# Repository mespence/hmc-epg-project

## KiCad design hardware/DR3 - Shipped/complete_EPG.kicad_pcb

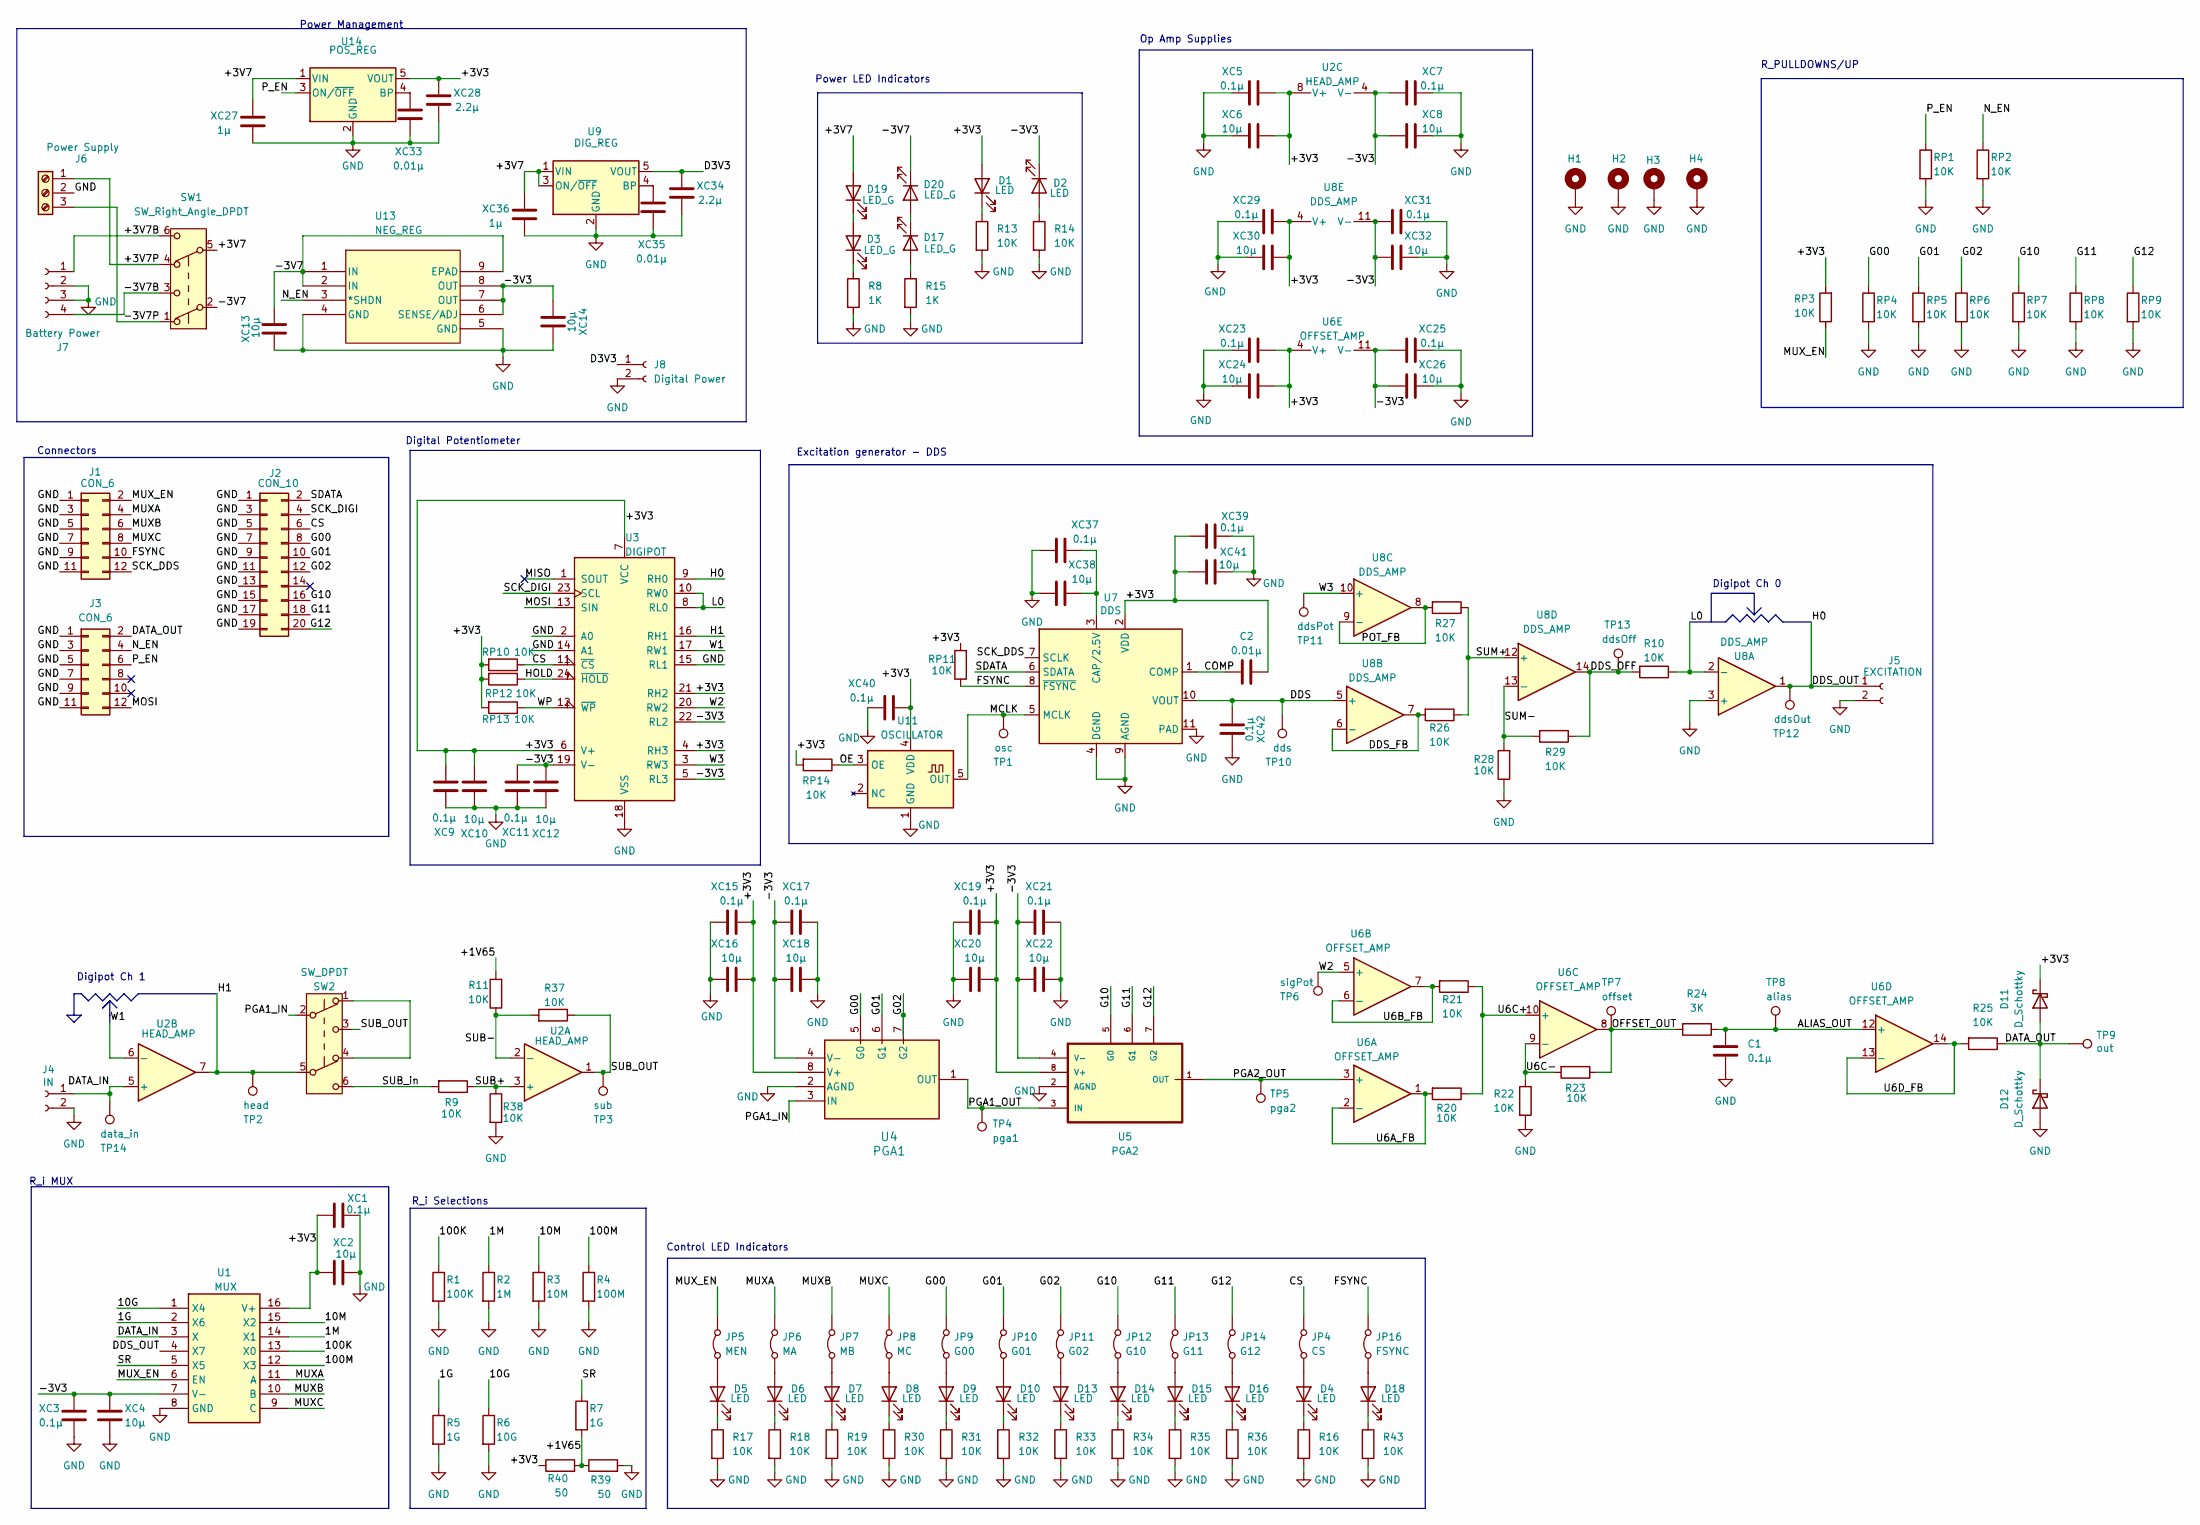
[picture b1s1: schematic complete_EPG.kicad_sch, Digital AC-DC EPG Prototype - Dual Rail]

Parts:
C1: 0.1μ; C_0805_2012Metric_Pad1.18x1.45mm_HandSolder
C2: 0.01μ; C_0805_2012Metric_Pad1.18x1.45mm_HandSolder
D1, D2, D4, D5, D6, D7, D8, D9, D10, D13, D14, D15, D16, D18: LED; LED_0805_2012Metric_Pad1.15x1.40mm_HandSolder; Mfg Part # LTST-C171KRKT
D3, D17, D19, D20: LED_G; LED_0805_2012Metric_Pad1.15x1.40mm_HandSolder; Mfg Part # LTST-C170KGKT
D11, D12: D_Schottky; D_0805_2012Metric_Pad1.15x1.40mm_HandSolder; Mfg Part # SD0805S040S0R1
H1, H2, H3, H4: MountingHole_Pad; MountingHole_3.2mm_M3_DIN965_Pad
J1, J3: CON_6; PinHeader_2x06_P2.54mm_Vertical; Mfg Part # IDSD-06-D-02.00-G
J2: CON_10; PinHeader_2x10_P2.54mm_Vertical; Mfg Part # IDSD-10-D-02.00-T-G
J4: IN; Right angle BNC 0731010120; Mfg Part # 0731010120
J5: EXCITATION; Right angle BNC 0731010120; Mfg Part # 0731010120
J6: Power Supply; Screw_Terminal_Power_Supply; Mfg Part # 1729131
J7: Battery Power; Screw_Terminal_Battery; Mfg Part # OSTVN04A150
J8: Digital Power; Screw_Terminal_Digital_Board; Mfg Part # OSTVN02A150
JP4: CS; SolderJumper-2_P1.3mm_Bridged_RoundedPad1.0x1.5mm
JP5: MEN; SolderJumper-2_P1.3mm_Bridged_RoundedPad1.0x1.5mm
JP6: MA; SolderJumper-2_P1.3mm_Bridged_RoundedPad1.0x1.5mm
JP7: MB; SolderJumper-2_P1.3mm_Bridged_RoundedPad1.0x1.5mm
JP8: MC; SolderJumper-2_P1.3mm_Bridged_RoundedPad1.0x1.5mm
JP9: G00; SolderJumper-2_P1.3mm_Bridged_RoundedPad1.0x1.5mm
JP10: G01; SolderJumper-2_P1.3mm_Bridged_RoundedPad1.0x1.5mm
JP11: G02; SolderJumper-2_P1.3mm_Bridged_RoundedPad1.0x1.5mm
JP12: G10; SolderJumper-2_P1.3mm_Bridged_RoundedPad1.0x1.5mm
JP13: G11; SolderJumper-2_P1.3mm_Bridged_RoundedPad1.0x1.5mm
JP14: G12; SolderJumper-2_P1.3mm_Bridged_RoundedPad1.0x1.5mm
JP16: FSYNC; SolderJumper-2_P1.3mm_Bridged_RoundedPad1.0x1.5mm
R1: 100K; R_0805_2012Metric_Pad1.20x1.40mm_HandSolder
R2: 1M; R_0805_2012Metric_Pad1.20x1.40mm_HandSolder
R3: 10M; R_0805_2012Metric_Pad1.20x1.40mm_HandSolder
R4: 100M; R_0805_2012Metric_Pad1.20x1.40mm_HandSolder
R5, R7: 1G; R_0805_2012Metric_Pad1.20x1.40mm_HandSolder
R6: 10G; R_0805_2012Metric_Pad1.20x1.40mm_HandSolder
R8, R15: 1K; R_0805_2012Metric_Pad1.20x1.40mm_HandSolder
R9, R10, R11, R13, R14, R16, R17, R18, R19, R20, R21, R22, R23, R25, R26, R27, R28, R29, R30, R31, R32, R33, R34, R35, R36, R37, R38, R43: 10K; R_0805_2012Metric_Pad1.20x1.40mm_HandSolder
R24: 3K; R_0805_2012Metric_Pad1.20x1.40mm_HandSolder
R39, R40: 50; R_0805_2012Metric_Pad1.20x1.40mm_HandSolder
RP1, RP2, RP3, RP4, RP5, RP6, RP7, RP8, RP9, RP10, RP11, RP12, RP13, RP14: 10K; R_0805_2012Metric_Pad1.20x1.40mm_HandSolder
SW1: SW_Right_Angle_DPDT; SW_E-Switch_EG2219_DPDT_Angled; Mfg Part # EG2219
SW2: SW_DPDT; SW_CK_JS202011CQN_DPDT_Straight; Mfg Part # JS202011CQN
TP1: osc; TestPoint_Pad_2.0x2.0mm
TP2: head; TestPoint_Pad_2.0x2.0mm
TP3: sub; TestPoint_Pad_2.0x2.0mm
TP4: pga1; TestPoint_Pad_2.0x2.0mm
TP5: pga2; TestPoint_Pad_2.0x2.0mm
TP6: sigPot; TestPoint_Pad_2.0x2.0mm
TP7: offset; TestPoint_Pad_2.0x2.0mm
TP8: alias; TestPoint_Pad_2.0x2.0mm
TP9: out; TestPoint_Pad_2.0x2.0mm
TP10: dds; TestPoint_Pad_2.0x2.0mm
TP11: ddsPot; TestPoint_Pad_2.0x2.0mm
TP12: ddsOut; TestPoint_Pad_2.0x2.0mm
TP13: ddsOff; TestPoint_Pad_2.0x2.0mm
TP14: data_in; TestPoint_Pad_2.0x2.0mm
U1: MUX; LIB_DG4051EEY-T1-GE3; Mfg Part # DG4051EEY-T1-GE3
U2: HEAD_AMP; SOIC-8_3.9x4.9mm_P1.27mm; Mfg Part # LMC662CMX/NOPB
U3: DIGIPOT; SOIC-24W_7.5x15.4mm_P1.27mm; Mfg Part # X9250US24Z-2.7T1
U4: PGA1; TSOT-23-8; Mfg Part # LTC6910-3CTS8-TRMPBF
U5: PGA2; TSOT-23-8; Mfg Part # LTC6910-1CTS8#PBF
U6: OFFSET_AMP; SOIC-14_3.9x8.7mm_P1.27mm; Mfg Part # TLV9104IDR
U7: DDS; LFCSP-WD-10-1EP_3x3mm_P0.5mm_EP1.64x2.38mm; Mfg Part # AD9837BCPZ-RL7
U8: DDS_AMP; SOIC-14_3.9x8.7mm_P1.27mm; Mfg Part # TLV9104IDR
U9: DIG_REG; SOT-23-5; Mfg Part # LP2985-33DBVRM3
U11: OSCILLATOR; TSOT-23-5; Mfg Part # SIT2024BIAS1-33E-16.000000
U13: NEG_REG; DFN-8_DD_LIT; Mfg Part # LT3015EDD-3.3#PBF
U14: POS_REG; SOT-23-5; Mfg Part # LP2985A-33DBVRM3
XC1, XC3, XC5, XC7, XC9, XC11, XC15, XC17, XC19, XC21, XC23, XC25, XC29, XC31, XC37, XC39, XC40, XC42: 0.1μ; C_0805_2012Metric_Pad1.18x1.45mm_HandSolder
XC2, XC4, XC6, XC8, XC10, XC12, XC13, XC14, XC16, XC18, XC20, XC22, XC24, XC26, XC30, XC32, XC38, XC41: 10μ; C_0805_2012Metric_Pad1.18x1.45mm_HandSolder
XC27, XC36: 1μ; C_0805_2012Metric_Pad1.18x1.45mm_HandSolder
XC28, XC34: 2.2μ; C_0805_2012Metric_Pad1.18x1.45mm_HandSolder
XC33, XC35: 0.01μ; C_0805_2012Metric_Pad1.18x1.45mm_HandSolder

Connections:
/1G: R5.1, U1.2 (X6)
/1M: R2.1, U1.14 (X1)
/10G: R6.1, U1.1 (X4)
/10M: R3.1, U1.15 (X2)
/100K: R1.1, U1.13 (X0)
/100M: R4.1, U1.12 (X3)
/+1V65: R7.2, R11.2, R39.1, R40.2
/+3V3: C2.2, D1.2 (A), D11.1 (K), R40.1, RP3.2, RP10.2, RP11.2, RP12.2, RP13.2, RP14.2, U1.16 (V+), U2.8 (V+), U3.4 (RH3), U3.6 (V+), U3.7 (VCC), U3.21 (RH2), U4.8 (V+), U5.8 (V+), U6.4 (V+), U7.2 (VDD), U8.4 (V+), U11.4 (VDD), U14.5 (VOUT), XC1.1, XC2.1, XC5.2, XC6.2, XC9.1, XC10.1, XC15.2, XC16.2, XC19.2, XC20.2, XC23.2, XC24.2, XC28.2, XC29.2, XC30.2, XC39.1, XC40.1, XC41.1
/+3V7: D19.2 (A), SW1.5 (B), U9.1 (VIN), U9.3 (ON/~OFF), U14.1 (VIN), XC27.2, XC36.2
/+3V7B: J7.1, SW1.6 (C)
/+3V7P: J6.1, SW1.4 (A)
/-3V3: D2.1 (K), U1.7 (V-), U2.4 (V-), U3.5 (RL3), U3.19 (V-), U3.22 (RL2), U4.4 (V-), U5.4 (V-), U6.11 (V-), U8.11 (V-), U13.6 (SENSE/ADJ), U13.7 (OUT), U13.8 (OUT), XC3.1, XC4.1, XC7.1, XC8.1, XC11.1, XC12.1, XC14.2, XC17.1, XC18.1, XC21.1, XC22.1, XC25.1, XC26.1, XC31.1, XC32.1
/-3V7: D20.1 (K), SW1.2 (B), U13.1 (IN), U13.2 (IN), U13.9 (EPAD), XC13.2
/-3V7B: J7.4, SW1.3 (C)
/-3V7P: J6.3, SW1.1 (A)
/ALIAS_OUT: C1.2, R24.1, TP8.1, U6.12 (+)
/COMP: C2.1, U7.1 (COMP)
/CS: J2.6, JP4.2 (B), RP10.1, U3.11 (~CS)
/D3V3: J8.1, U9.5 (VOUT), XC34.2
/DATA_IN: J4.1, TP14.1, U1.3 (X), U2.5 (+)
/DATA_OUT: D11.2 (A), D12.1 (K), J3.2, R25.1, TP9.1
/DDS: TP10.1, U7.10 (VOUT), U8.5 (+), XC42.1
/DDS_FB: R26.2, U8.6 (-), U8.7
/DDS_OFF: R10.2, R29.1, TP13.1, U8.14
/DDS_OUT: J5.1, TP12.1, U1.4 (X7), U3.9 (RH0), U8.1
/FSYNC: J1.10, JP16.2 (B), RP11.1, U7.8 (~FSYNC)
/G00: J2.8, JP9.2 (B), RP4.1, U4.5 (G0)
/G01: J2.10, JP10.2 (B), RP5.1, U4.6 (G1)
/G02: J2.12, JP11.2 (B), RP6.1, U4.7 (G2)
/G10: J2.16, JP12.2 (B), RP7.1, U5.5 (G0)
/G11: J2.18, JP13.2 (B), RP8.1, U5.6 (G1)
/G12: J2.20, JP14.2 (B), RP9.1, U5.7 (G2)
/H1: SW2.5 (B), TP2.1, U2.7, U3.16 (RH1)
/HOLD: RP12.1, U3.24 (~HOLD)
/L0: R10.1, U3.8 (RL0), U3.10 (RW0), U8.2 (-)
/MCLK: TP1.1, U7.5 (MCLK), U11.5 (OUT)
/MISO: U3.1 (SOUT)
/MOSI: J3.12, U3.13 (SIN)
/MUXA: J1.4, JP6.2 (B), U1.11 (A)
/MUXB: J1.6, JP7.2 (B), U1.10 (B)
/MUXC: J1.8, JP8.2 (B), U1.9 (C)
/MUX_EN: J1.2, JP5.2 (B), RP3.1, U1.6 (EN)
/N_EN: J3.4, RP2.1, U13.3 (*SHDN)
/OE: RP14.1, U11.3 (OE)
/OFFSET_OUT: R23.1, R24.2, TP7.1, U6.8
/PGA1_IN: SW2.2 (B), U4.3 (IN)
/PGA1_OUT: TP4.1, U4.1 (OUT), U5.3 (IN)
/PGA2_OUT: TP5.1, U5.1 (OUT), U6.3 (+)
/POT_FB: R27.2, U8.8, U8.9 (-)
/P_EN: J3.6, RP1.1, U14.3 (ON/~OFF)
/SCK_DDS: J1.12, U7.7 (SCLK)
/SCK_DIGI: J2.4, U3.23 (SCL)
/SDATA: J2.2, U7.6 (SDATA)
/SR: R7.1, U1.5 (X5)
/SUB+: R9.1, R38.1, U2.3 (+)
/SUB-: R11.1, R37.2, U2.2 (-)
/SUB_OUT: R37.1, SW2.3 (C), TP3.1, U2.1
/SUB_in: R9.2, SW2.6 (C)
/SUM+: R26.1, R27.1, U8.12 (+)
/SUM-: R28.2, R29.2, U8.13 (-)
/U6A_FB: R20.2, U6.1, U6.2 (-)
/U6B_FB: R21.2, U6.6 (-), U6.7
/U6C+: R20.1, R21.1, U6.10 (+)
/U6C-: R22.1, R23.2, U6.9 (-)
/U6D_FB: R25.2, U6.13 (-), U6.14
/W1: U2.6 (-), U3.17 (RW1)
/W2: TP6.1, U3.20 (RW2), U6.5 (+)
/W3: TP11.1, U3.3 (RW3), U8.10 (+)
/WP: RP13.1, U3.12 (~WP)
GND: C1.1, D12.2 (A), H1.1, H2.1, H3.1, H4.1, J1.1, J1.3, J1.5, J1.7, J1.9, J1.11, J2.1, J2.3, J2.5, J2.7, J2.9, J2.11, J2.13, J2.15, J2.17, J2.19, J3.1, J3.3, J3.5, J3.7, J3.9, J3.11, J4.2, J5.2, J6.2, J7.2, J7.3, J8.2, R1.2, R2.2, R3.2, R4.2, R5.2, R6.2, R8.2, R13.2, R14.2, R15.2, R16.2, R17.2, R18.2, R19.2, R22.2, R28.1, R30.2, R31.2, R32.2, R33.2, R34.2, R35.2, R36.2, R38.2, R39.2, R43.2, RP1.2, RP2.2, RP4.2, RP5.2, RP6.2, RP7.2, RP8.2, RP9.2, U1.8 (GND), U3.2 (A0), U3.14 (A1), U3.15 (RL1), U3.18 (VSS), U4.2 (AGND), U5.2 (AGND), U7.4 (DGND), U7.9 (AGND), U7.11 (PAD), U8.3 (+), U9.2 (GND), U11.1 (GND), U13.4 (GND), U13.5 (GND), U14.2 (GND), XC1.2, XC2.2, XC3.2, XC4.2, XC5.1, XC6.1, XC7.2, XC8.2, XC9.2, XC10.2, XC11.2, XC12.2, XC13.1, XC14.1, XC15.1, XC16.1, XC17.2, XC18.2, XC19.1, XC20.1, XC21.2, XC22.2, XC23.1, XC24.1, XC25.2, XC26.2, XC27.1, XC28.1, XC29.1, XC30.1, XC31.2, XC32.2, XC33.1, XC34.1, XC35.1, XC36.1, XC37.2, XC38.2, XC39.2, XC40.2, XC41.2, XC42.2
unnamed: D1.1 (K), R13.1
unnamed: D2.2 (A), R14.1
unnamed: D3.1 (K), R8.1
unnamed: D4.2 (A), JP4.1 (A)
unnamed: D4.1 (K), R16.1
unnamed: D5.2 (A), JP5.1 (A)
unnamed: D5.1 (K), R17.1
unnamed: D6.2 (A), JP6.1 (A)
unnamed: D6.1 (K), R18.1
unnamed: D7.2 (A), JP7.1 (A)
unnamed: D7.1 (K), R19.1
unnamed: D8.2 (A), JP8.1 (A)
unnamed: D8.1 (K), R30.1
unnamed: D9.2 (A), JP9.1 (A)
unnamed: D9.1 (K), R31.1
unnamed: D10.2 (A), JP10.1 (A)
unnamed: D10.1 (K), R32.1
unnamed: D13.2 (A), JP11.1 (A)
unnamed: D13.1 (K), R33.1
unnamed: D14.2 (A), JP12.1 (A)
unnamed: D14.1 (K), R34.1
unnamed: D15.2 (A), JP13.1 (A)
unnamed: D15.1 (K), R35.1
unnamed: D16.2 (A), JP14.1 (A)
unnamed: D16.1 (K), R36.1
unnamed: D17.2 (A), R15.1
unnamed: D17.1 (K), D20.2 (A)
unnamed: D18.2 (A), JP16.1 (A)
unnamed: D18.1 (K), R43.1
unnamed: D3.2 (A), D19.1 (K)
unnamed: SW2.1 (A), SW2.4 (A)
unnamed: U7.3 (CAP/2.5V), XC37.1, XC38.1
unnamed: U9.4 (BP), XC35.2
unnamed: U14.4 (BP), XC33.2

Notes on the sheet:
Digital Potentiometer
Digipot Ch 1
R_PULLDOWNS/UP
Op Amp Supplies
Connectors
Power LED Indicators
R_i Selections
Power Management
Digipot Ch 0
Control LED Indicators
R_i MUX
Excitation generator - DDS

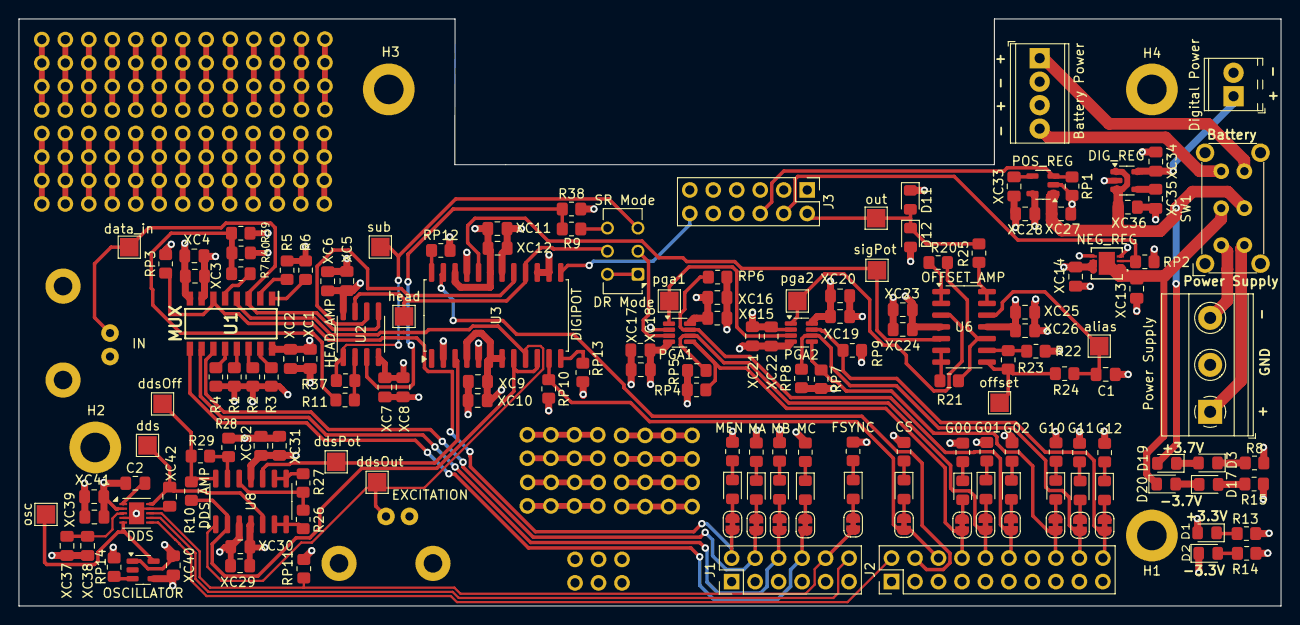
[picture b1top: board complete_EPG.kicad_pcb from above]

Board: 4 copper layers, 136.5 x 63.5 mm, 170 parts (0 on the bottom side), 103 nets.

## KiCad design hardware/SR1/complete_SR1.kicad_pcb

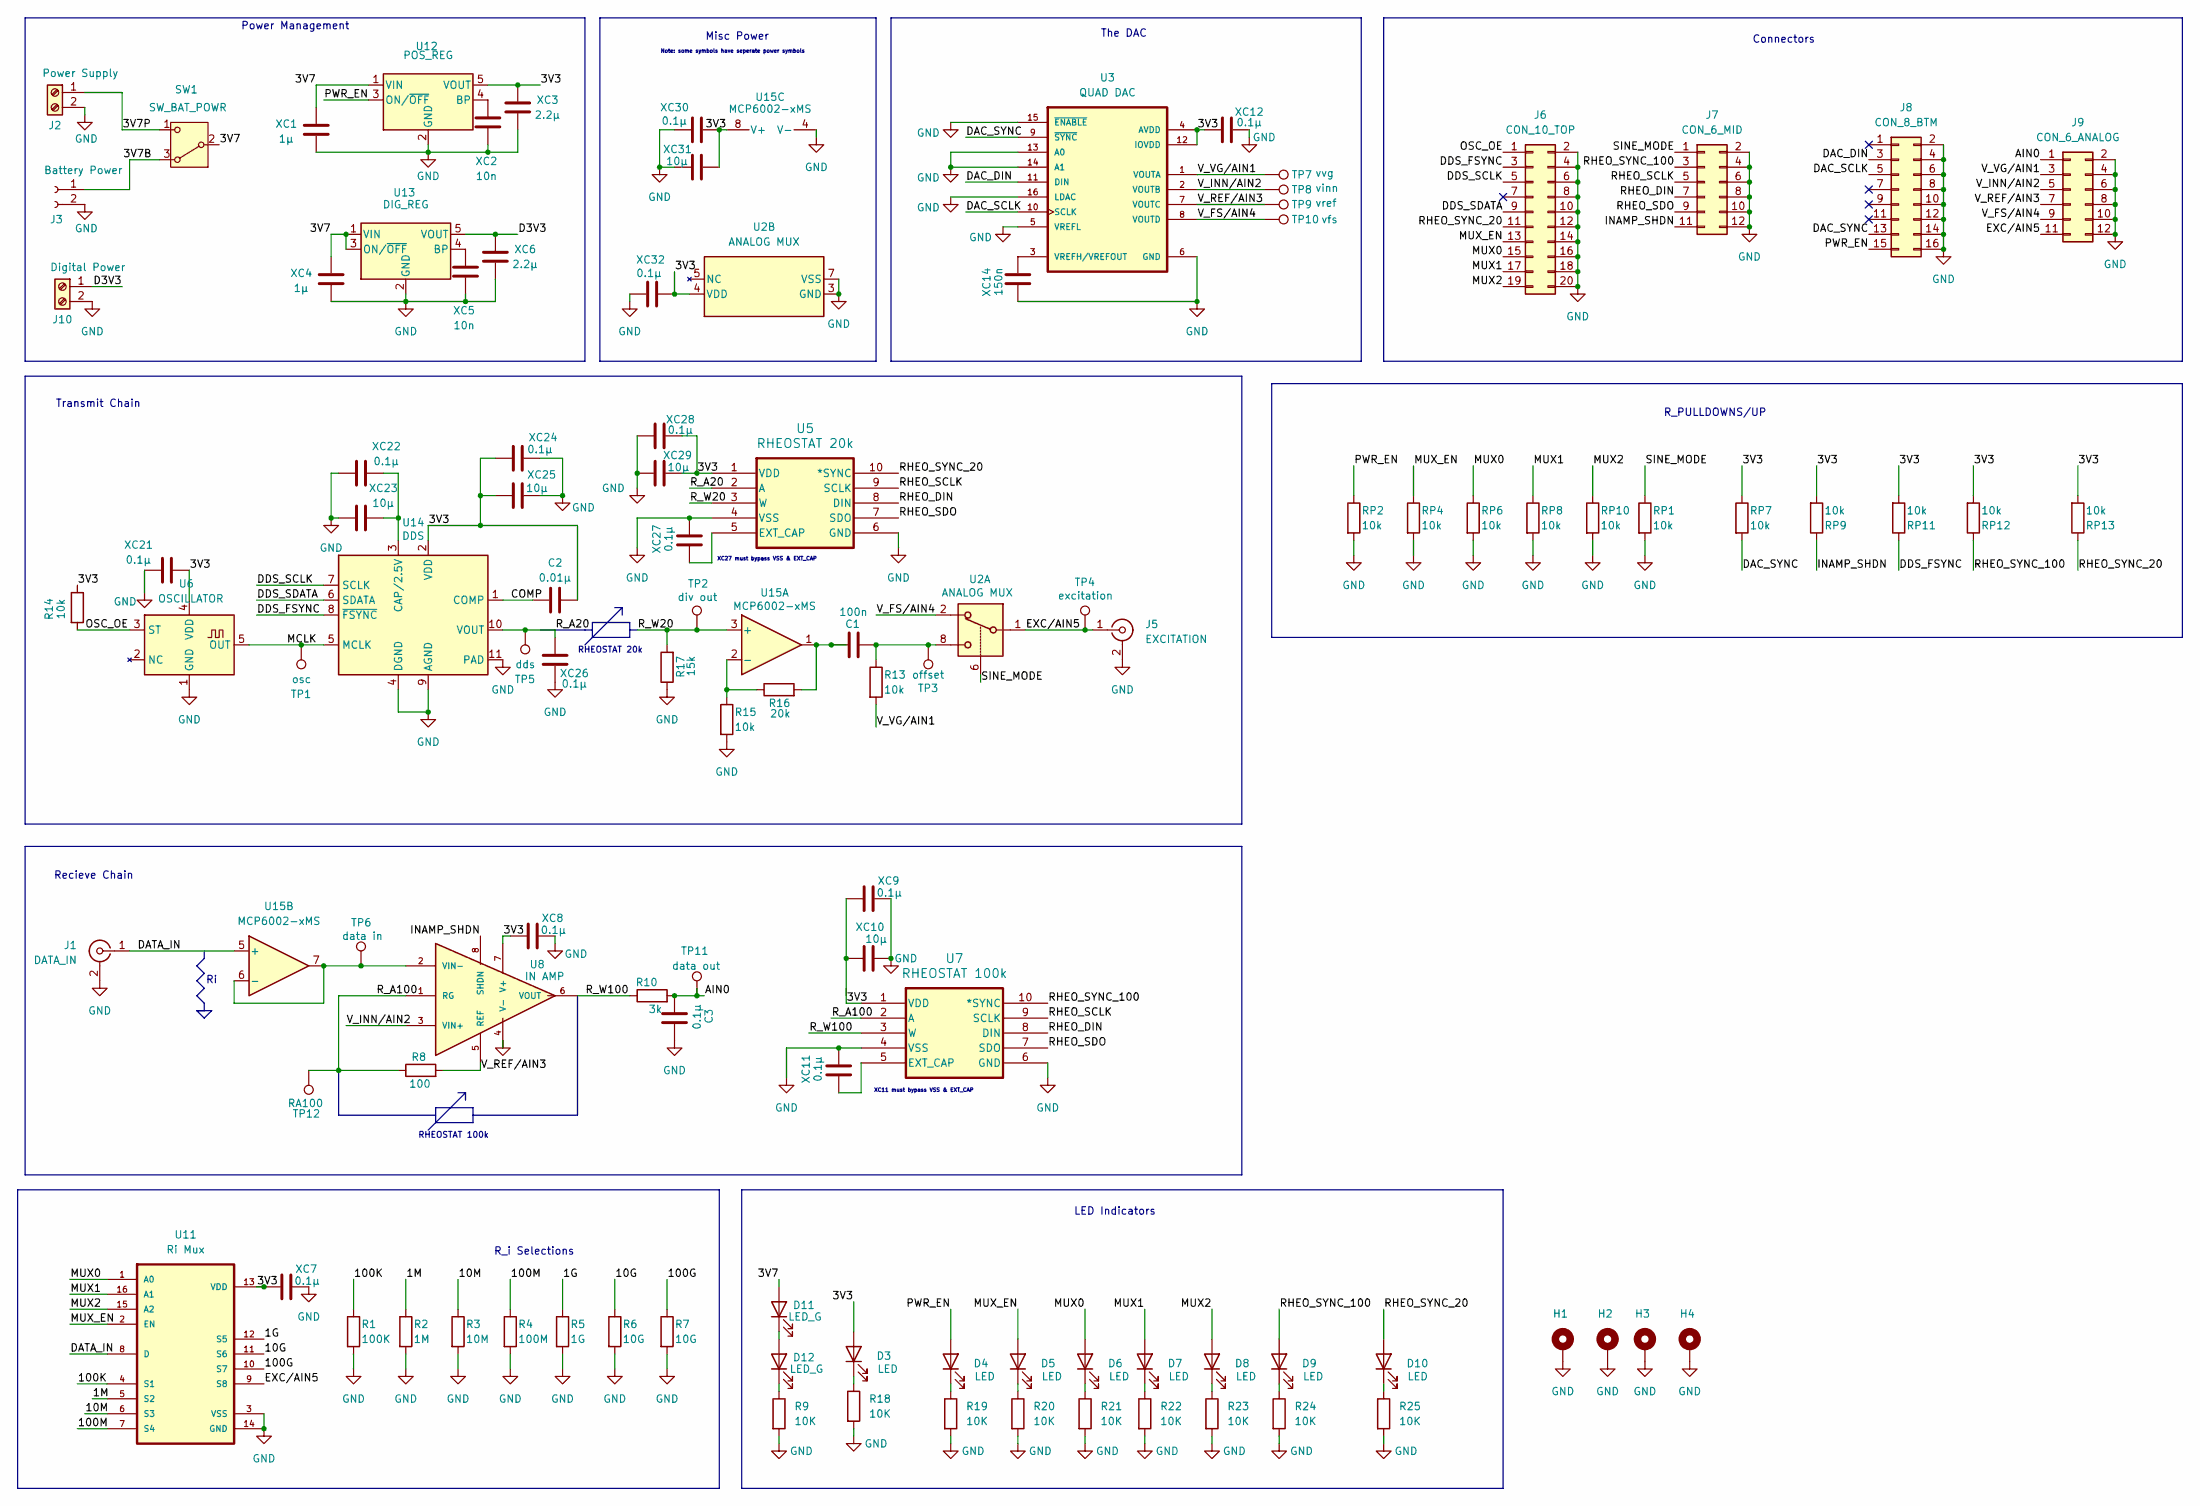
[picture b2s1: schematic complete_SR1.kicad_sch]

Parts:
C1: 100n; C_0805_2012Metric_Pad1.18x1.45mm_HandSolder
C2: 0.01μ; C_0805_2012Metric_Pad1.18x1.45mm_HandSolder
C3: 0.1μ; C_0805_2012Metric_Pad1.18x1.45mm_HandSolder
D3, D4, D5, D6, D7, D8, D9, D10: LED; LED_0805_2012Metric_Pad1.15x1.40mm_HandSolder
D11, D12: LED_G; LED_0805_2012Metric_Pad1.15x1.40mm_HandSolder; Mfg Part # LTST-C170KGKT
H1, H2, H3, H4: MountingHole_Pad; MountingHole_3.2mm_M3_DIN965_Pad
J1: DATA_IN; Right angle BNC 0731010120
J2: Power Supply; TerminalBlock_Phoenix_MKDS-1,5-2-5.08_1x02_P5.08mm_Horizont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
J3: Battery Power; CONN02_530480210_MOL; Mfg Part # WM1742-ND
J5: EXCITATION; Right angle BNC 0731010120
J6: CON_10_TOP; PinHeader_2x10_P2.54mm_Vertical; Mfg Part # IDSD-10-D-02.00-T-G
J7: CON_6_MID; PinHeader_2x06_P2.54mm_Vertical
J8: CON_8_BTM; PinHeader_2x08_P2.54mm_Vertical
J9: CON_6_ANALOG; PinHeader_2x06_P2.54mm_Vertical
J10: Digital Power; JST_SHL_SM02B-SHLS-TF_1x02-1MP_P1.00mm_Horizontal; Mfg Part # 455-SM02B-SHLS-TFCT-ND
R1: 100K; R_0805_2012Metric_Pad1.20x1.40mm_HandSolder
R2: 1M; R_0805_2012Metric_Pad1.20x1.40mm_HandSolder
R3: 10M; R_0805_2012Metric_Pad1.20x1.40mm_HandSolder
R4: 100M; R_0805_2012Metric_Pad1.20x1.40mm_HandSolder
R5: 1G; R_0805_2012Metric_Pad1.20x1.40mm_HandSolder
R6, R7: 10G; R_0805_2012Metric_Pad1.20x1.40mm_HandSolder
R8: 100; R_0805_2012Metric_Pad1.20x1.40mm_HandSolder
R9, R18, R19, R20, R21, R22, R23, R24, R25: 10K; R_0805_2012Metric_Pad1.20x1.40mm_HandSolder
R10: 3k; R_0805_2012Metric_Pad1.20x1.40mm_HandSolder
R13, R14, R15: 10k; R_0805_2012Metric_Pad1.20x1.40mm_HandSolder
R16: 20k; R_0805_2012Metric_Pad1.20x1.40mm_HandSolder
R17: 15k; R_0805_2012Metric_Pad1.20x1.40mm_HandSolder
RP1, RP2, RP4, RP6, RP7, RP8, RP9, RP10, RP11, RP12, RP13: 10k; R_0805_2012Metric_Pad1.20x1.40mm_HandSolder
SW1: SW_BAT_POWR; SW_E-Switch_EG1224_SPDT_Angled; Mfg Part # EG2585-ND
TP1: osc; TestPoint_Pad_2.0x2.0mm
TP2: div out; TestPoint_Pad_2.0x2.0mm
TP3: offset; TestPoint_Pad_2.0x2.0mm
TP4: excitation; TestPoint_Pad_2.0x2.0mm
TP5: dds; TestPoint_Pad_2.0x2.0mm
TP6: data in; TestPoint_Pad_2.0x2.0mm
TP7: vvg; TestPoint_Pad_2.0x2.0mm
TP8: vinn; TestPoint_Pad_2.0x2.0mm
TP9: vref; TestPoint_Pad_2.0x2.0mm
TP10: vfs; TestPoint_Pad_2.0x2.0mm
TP11: data out; TestPoint_Pad_2.0x2.0mm
TP12: RA100; TestPoint_Pad_2.0x2.0mm
U2: ANALOG MUX; MSOP-8_3x3mm_P0.65mm; Mfg Part # ADG619BRMZ-REEL7CT-ND
U3: QUAD DAC; TSSOP-16_4.4x5mm_P0.65mm; Mfg Part # 296-DAC7564IAPWRCT-ND
U5: RHEOSTAT 20k; RM_10_ADI; Mfg Part # AD5270BRMZ-20-RL7CT-ND
U6: OSCILLATOR; TSOT-23-5; Mfg Part # SIT2024BIAS1-33E-16.000000
U7: RHEOSTAT 100k; RM_10_ADI; Mfg Part # AD5270BRMZ-100-RL7CT-ND
U8: IN AMP; VSSOP-8_3x3mm_P0.65mm; Mfg Part # 296-12204-1-ND
U11: Ri Mux; TSSOP-16_4.4x5mm_P0.65mm; Mfg Part # 296-53256-1-ND
U12: POS_REG; SOT-23-5; Mfg Part # LP2985A-33DBVRM3
U13: DIG_REG; SOT-23-5; Mfg Part # LP2985A-33DBVRM3
U14: DDS; LFCSP-WD-10-1EP_3x3mm_P0.5mm_EP1.64x2.38mm; Mfg Part # AD9837BCPZ-RL7
U15: MCP6002-xMS; MSOP8_MC_MCH; Mfg Part # MCP6002T-I/MSCT-ND
XC1, XC4: 1μ; C_0805_2012Metric_Pad1.18x1.45mm_HandSolder
XC2, XC5: 10n; C_0805_2012Metric_Pad1.18x1.45mm_HandSolder
XC3, XC6: 2.2μ; C_0805_2012Metric_Pad1.18x1.45mm_HandSolder
XC7, XC8, XC9, XC11, XC12, XC21, XC22, XC24, XC26, XC27, XC28, XC30, XC32: 0.1μ; C_0805_2012Metric_Pad1.18x1.45mm_HandSolder
XC10, XC23, XC25, XC29, XC31: 10μ; C_0805_2012Metric_Pad1.18x1.45mm_HandSolder
XC14: 150n; C_0805_2012Metric_Pad1.18x1.45mm_HandSolder

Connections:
/1G: R5.1, U11.12 (S5)
/1M: R2.1, U11.5 (S2)
/3V3: C2.2, D3.2 (A), R14.1, RP7.1, RP9.2, RP11.2, RP12.2, RP13.2, U2.4 (VDD), U3.4 (AVDD), U3.12 (IOVDD), U5.1 (VDD), U6.4 (VDD), U7.1 (VDD), U8.7 (V+), U11.13 (VDD), U12.5 (VOUT), U14.2 (VDD), U15.8 (V+), XC3.2, XC7.1, XC8.1, XC9.1, XC10.1, XC12.1, XC21.1, XC24.1, XC25.1, XC28.2, XC29.1, XC30.1, XC31.1, XC32.2
/3V7: D11.2 (A), SW1.2 (B), U12.1 (VIN), U13.1 (VIN), U13.3 (ON/~OFF), XC1.2, XC4.2
/3V7B: J3.1, SW1.3 (A)
/3V7P: J2.1, SW1.1 (C)
/10G: R6.1, U11.11 (S6)
/10M: R3.1, U11.6 (S3)
/100G: R7.1, U11.10 (S7)
/100K: R1.1, U11.4 (S1)
/100M: R4.1, U11.7 (S4)
/AIN0: C3.1, J9.1, R10.2, TP11.1
/COMP: C2.1, U14.1 (COMP)
/D3V3: J10.1, U13.5 (VOUT), XC6.2
/DAC_DIN: J8.3, U3.11 (DIN)
/DAC_SCLK: J8.5, U3.10 (SCLK)
/DAC_SYNC: J8.13, RP7.2, U3.9 (~SYNC)
/DATA_IN: J1.1 (In), U11.8 (D), U15.5 (+)
/DDS_FSYNC: J6.3, RP11.1, U14.8 (~FSYNC)
/DDS_SCLK: J6.5, U14.7 (SCLK)
/DDS_SDATA: J6.9, U14.6 (SDATA)
/EXC/AIN5: J5.1 (In), J9.11, TP4.1, U2.1, U11.9 (S8)
/INAMP_SHDN: J7.11, RP9.1, U8.8 (SHDN)
/MCLK: TP1.1, U6.5 (OUT), U14.5 (MCLK)
/MUX0: D6.2 (A), J6.15, RP6.1, U11.1 (A0)
/MUX1: D7.2 (A), J6.17, RP8.1, U11.16 (A1)
/MUX2: D8.2 (A), J6.19, RP10.1, U11.15 (A2)
/MUX_EN: D5.2 (A), J6.13, RP4.1, U11.2 (EN)
/OSC_OE: J6.1, R14.2, U6.3 (ST)
/PWR_EN: D4.2 (A), J8.15, RP2.1, U12.3 (ON/~OFF)
/RHEO_DIN: J7.7, U5.8 (DIN), U7.8 (DIN)
/RHEO_SCLK: J7.5, U5.9 (SCLK), U7.9 (SCLK)
/RHEO_SDO: J7.9, U5.7 (SDO), U7.7 (SDO)
/RHEO_SYNC_20: D10.2 (A), J6.11, RP13.1, U5.10 (*SYNC)
/RHEO_SYNC_100: D9.2 (A), J7.3, RP12.1, U7.10 (*SYNC)
/R_A20: TP5.1, U5.2 (A), U14.10 (VOUT), XC26.1
/R_A100: R8.1, TP12.1, U7.2 (A), U8.1 (RG)
/R_W20: R17.2, TP2.1, U5.3 (W), U15.3 (+)
/R_W100: R10.1, U7.3 (W), U8.6 (VOUT)
/SINE_MODE: J7.1, RP1.1, U2.6
/V_FS/AIN4: J9.9, TP10.1, U2.2, U3.8 (VOUTD)
/V_INN/AIN2: J9.5, TP8.1, U3.2 (VOUTB), U8.3 (VIN+)
/V_REF/AIN3: J9.7, R8.2, TP9.1, U3.7 (VOUTC), U8.5 (REF)
/V_VG/AIN1: J9.3, R13.2, TP7.1, U3.1 (VOUTA)
GND: C3.2, H1.1, H2.1, H3.1, H4.1, J1.2 (Ext), J2.2, J3.2, J5.2 (Ext), J6.2, J6.4, J6.6, J6.8, J6.10, J6.12, J6.14, J6.16, J6.18, J6.20, J7.2, J7.4, J7.6, J7.8, J7.10, J7.12, J8.2, J8.4, J8.6, J8.8, J8.10, J8.12, J8.14, J8.16, J9.2, J9.4, J9.6, J9.8, J9.10, J9.12, J10.2, R1.2, R2.2, R3.2, R4.2, R5.2, R6.2, R7.2, R9.2, R15.2, R17.1, R18.2, R19.2, R20.2, R21.2, R22.2, R23.2, R24.2, R25.2, RP1.2, RP2.2, RP4.2, RP6.2, RP8.2, RP10.2, U2.3 (GND), U2.7 (VSS), U3.5 (VREFL), U3.6 (GND), U3.13 (A0), U3.14 (A1), U3.15 (~ENABLE), U3.16 (LDAC), U5.4 (VSS), U5.6 (GND), U6.1 (GND), U7.4 (VSS), U7.6 (GND), U8.4 (V-), U11.3 (VSS), U11.14 (GND), U12.2 (GND), U13.2 (GND), U14.4 (DGND), U14.9 (AGND), U14.11 (PAD), U15.4 (V-), XC1.1, XC2.1, XC3.1, XC4.1, XC5.1, XC6.1, XC7.2, XC8.2, XC9.2, XC10.2, XC11.2, XC12.2, XC14.1, XC21.2, XC22.2, XC23.2, XC24.2, XC25.2, XC26.2, XC27.2, XC28.1, XC29.2, XC30.2, XC31.2, XC32.1
unnamed: C1.1, R13.1, TP3.1, U2.8
unnamed: C1.2, R16.2, U15.1
unnamed: D3.1 (K), R18.1
unnamed: D4.1 (K), R19.1
unnamed: D5.1 (K), R20.1
unnamed: D6.1 (K), R21.1
unnamed: D7.1 (K), R22.1
unnamed: D8.1 (K), R23.1
unnamed: D9.1 (K), R24.1
unnamed: D10.1 (K), R25.1
unnamed: D11.1 (K), D12.2 (A)
unnamed: D12.1 (K), R9.1
unnamed: U3.3 (VREFH/VREFOUT), XC14.2
unnamed: U5.5 (EXT_CAP), XC27.1
unnamed: U7.5 (EXT_CAP), XC11.1
unnamed: U12.4 (BP), XC2.2
unnamed: U13.4 (BP), XC5.2
unnamed: U14.3 (CAP/2.5V), XC22.1, XC23.1
unnamed: R15.1, R16.1, U15.2 (-)
unnamed: TP6.1, U8.2 (VIN-), U15.6 (-), U15.7

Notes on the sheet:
XC27 must bypass VSS & EXT_CAP
Note: some symbols have seperate power symbols
Connectors
LED Indicators
RHEOSTAT 20k
The DAC
R_PULLDOWNS/UP
Misc Power
Power Management
Recieve Chain
Transmit Chain
R_i Selections
RHEOSTAT 100k
XC11 must bypass VSS & EXT_CAP

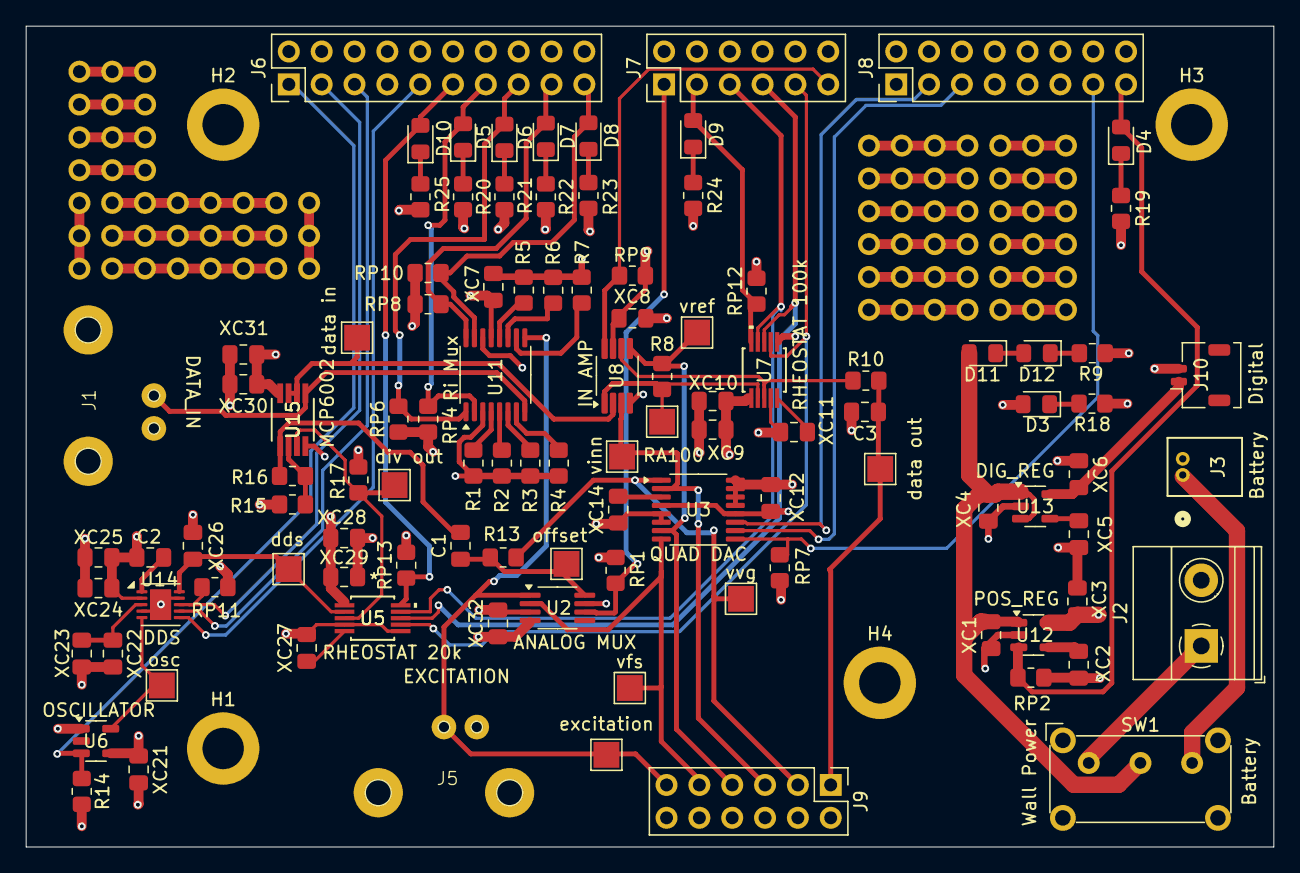
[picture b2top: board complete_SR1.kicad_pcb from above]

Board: 4 copper layers, 96.5 x 63.5 mm, 109 parts (0 on the bottom side), 65 nets.

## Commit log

2025-09-26 WIP BLE code for device monitor testing
2025-09-26 new device view tab exploration
2025-10-03 Refactor DevicePanel and consolidate its components
2025-10-03 Move icons and fonts to resources folder
2025-10-03 update data buffer to be owned by live view tab, and device monitoring and live view access it. updated device view to accept testing script and fixed time axis (10 seconds ago)
2025-10-10 fixed scrolling issues and fixed bottom axis issues in device view
2025-10-14 Updates for swarthmore students
2025-10-15 Added IntroLab for SwarthmoreTeam
2025-10-16 Enhance IntroLab with timeseries model suggestions
    Added suggestions for timeseries feature extraction and classification.
2025-10-16 Fix formatting of suggestions in IntroLab notebook
2025-10-24 debug device monitor seconds ago axis, debugging baseline behavior in device view
2025-10-31 Detach sliders from ENGR UI, overhaul them to be dynamically generated from a YAML spec
2025-10-31 Move bluetooth files to /epg_board, rename BluetoothState to BluetoothStateChecker
2025-10-31 Remove all socket code (no longer needed since porting the ENGR sliders to SCIDO)
2025-11-07 Draft new bluetooth handler
2025-11-14 Refactor bluetooth handler
2025-11-14 Integrate BLE handler to UI (but device panel needs revision)
2025-11-14 Refactor Device Panel widgets, reduce likelihood of QTimer "stopped from other thread" warning, and reorder imports in live_view
2025-11-14 Missing device panel files from previous commit
2025-11-16 Fix bug preventing an app close from being canceled.
2025-11-16 Update BLE tester, minor changes to BLE code
2025-11-16 Tweak imports for files with main guards, rename spec to indicate it's for DR3
2025-11-17 Streamline device panel connection code, working for single device
2025-11-21 Remove windows-only checks for the device panel
2025-11-26 Uploaded SR1 KiCad files
2025-11-26 Uploaded Shipped DR3 KiCad Files
2025-11-26 Added hardware KiCad .gitignore
